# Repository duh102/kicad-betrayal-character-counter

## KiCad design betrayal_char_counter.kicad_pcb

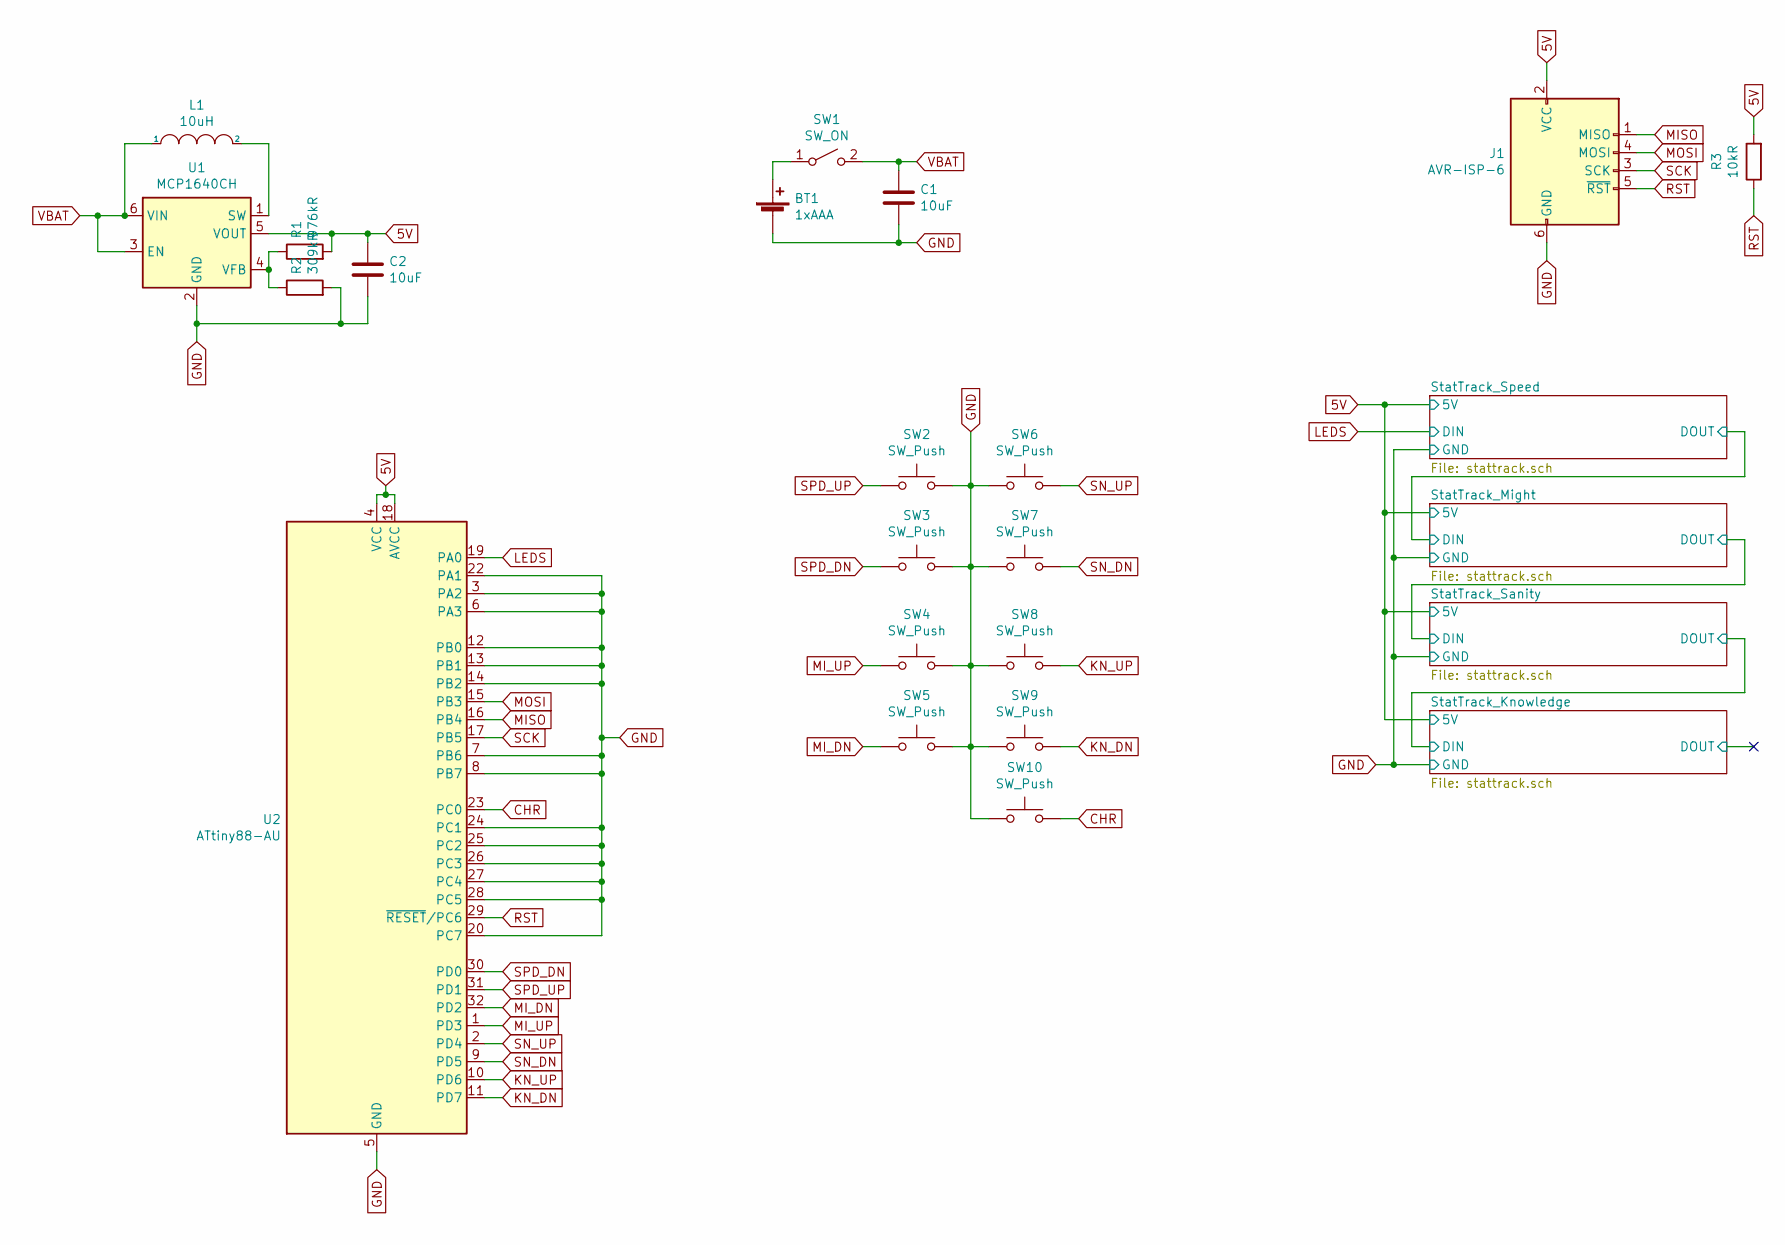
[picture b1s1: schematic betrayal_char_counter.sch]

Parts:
BT1: 1xAAA; BatteryHolder_Keystone_2466_1xAAA
C1, C2: 10uF; C_0805_2012Metric
J1: AVR-ISP-6; PinHeader_2x03_P2.54mm_Vertical_SMD
L1: 10uH; L_Taiyo-Yuden_NR-50xx
R1: 976kR; R_0805_2012Metric
R2: 309kR; R_0805_2012Metric
R3: 10kR; R_0805_2012Metric
SW1: SW_ON; SW_Slide_1P2T_CK_OS102011MS2Q
SW2, SW3, SW4, SW5, SW6, SW7, SW8, SW9, SW10: SW_Push; SW_SPST_SKQG_WithoutStem
U1: MCP1640CH; SOT-23-6
U2: ATtiny88-AU; TQFP-32_7x7mm_P0.8mm

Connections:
5V: C2.1, J1.2 (VCC), R1.2, R3.2, U1.5 (VOUT), U2.4 (VCC), U2.18 (AVCC); also elsewhere on the board
CHR: SW10.2, U2.23 (PC0)
GND: BT1.2 (-), C1.2, C2.2, J1.6 (GND), R2.2, SW2.2, SW3.2, SW4.2, SW5.2, SW6.1, SW7.1, SW8.1, SW9.1, SW10.1, U1.2 (GND), U2.3 (PA2), U2.5 (GND), U2.6 (PA3), U2.7 (PB6), U2.8 (PB7), U2.12 (PB0), U2.13 (PB1), U2.14 (PB2), U2.20 (PC7), U2.21 (GND), U2.22 (PA1), U2.24 (PC1), U2.25 (PC2), U2.26 (PC3), U2.27 (PC4), U2.28 (PC5); also elsewhere on the board
KN_DN: SW9.2, U2.11 (PD7)
KN_UP: SW8.2, U2.10 (PD6)
LEDS: U2.19 (PA0); also elsewhere on the board
MISO: J1.1 (MISO), U2.16 (PB4)
MI_DN: SW5.1, U2.32 (PD2)
MI_UP: SW4.1, U2.1 (PD3)
MOSI: J1.4 (MOSI), U2.15 (PB3)
unnamed: BT1.1 (+), SW1.1 (A)
unnamed: L1.2, U1.1 (SW)
unnamed: R1.1, R2.1, U1.4 (VFB)
RST: J1.5 (~RST), R3.1, U2.29 (~RESET~/PC6)
SCK: J1.3 (SCK), U2.17 (PB5)
SN_DN: SW7.2, U2.9 (PD5)
SN_UP: SW6.2, U2.2 (PD4)
SPD_DN: SW3.1, U2.30 (PD0)
SPD_UP: SW2.1, U2.31 (PD1)
VBAT: C1.1, L1.1, SW1.2 (B), U1.3 (EN), U1.6 (VIN)

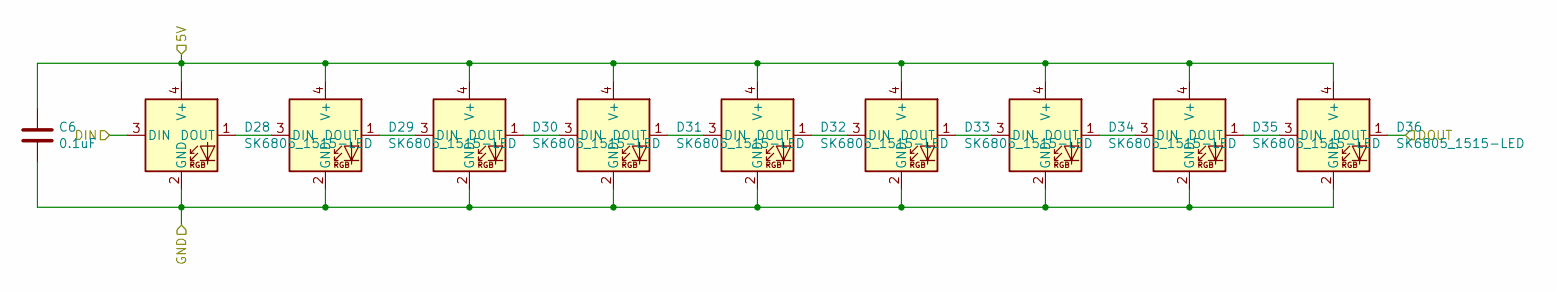
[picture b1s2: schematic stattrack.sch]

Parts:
C3: 0.1uF; C_0805_2012Metric
D1, D2, D3, D4, D5, D6, D7, D8, D9: SK6805_1515-LED; LED_SK6805_PLCC4_1.5x1.5mm_P0.65mm

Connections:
5V: C3.1, D1.4 (V+), D2.4 (V+), D3.4 (V+), D4.4 (V+), D5.4 (V+), D6.4 (V+), D7.4 (V+), D8.4 (V+), D9.4 (V+); also elsewhere on the board
/StatTrack_Might/DIN: D9.1 (DOUT); also elsewhere on the board
GND: C3.2, D1.2 (GND), D2.2 (GND), D3.2 (GND), D4.2 (GND), D5.2 (GND), D6.2 (GND), D7.2 (GND), D8.2 (GND), D9.2 (GND); also elsewhere on the board
LEDS: D1.3 (DIN); also elsewhere on the board
unnamed: D1.1 (DOUT), D2.3 (DIN)
unnamed: D2.1 (DOUT), D3.3 (DIN)
unnamed: D3.1 (DOUT), D4.3 (DIN)
unnamed: D4.1 (DOUT), D5.3 (DIN)
unnamed: D5.1 (DOUT), D6.3 (DIN)
unnamed: D6.1 (DOUT), D7.3 (DIN)
unnamed: D7.1 (DOUT), D8.3 (DIN)
unnamed: D8.1 (DOUT), D9.3 (DIN)

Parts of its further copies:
C4, C5, C6: 0.1uF; C_0805_2012Metric
D10, D11, D12, D13, D14, D15, D16, D17, D18, D19, D20, D21, D22, D23, D24, D25, D26, D27, D28, D29, D30, D31, D32, D33, D34, D35, D36: SK6805_1515-LED; LED_SK6805_PLCC4_1.5x1.5mm_P0.65mm

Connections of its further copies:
5V: C4.1, C5.1, C6.1, D10.4 (V+), D11.4 (V+), D12.4 (V+), D13.4 (V+), D14.4 (V+), D15.4 (V+), D16.4 (V+), D17.4 (V+), D18.4 (V+), D19.4 (V+), D20.4 (V+), D21.4 (V+), D22.4 (V+), D23.4 (V+), D24.4 (V+), D25.4 (V+), D26.4 (V+), D27.4 (V+), D28.4 (V+), D29.4 (V+), D30.4 (V+), D31.4 (V+), D32.4 (V+), D33.4 (V+), D34.4 (V+), D35.4 (V+), D36.4 (V+); also elsewhere on the board
/StatTrack_Knowledge/DIN: D27.1 (DOUT), D28.3 (DIN)
/StatTrack_Might/DIN: D10.3 (DIN); also elsewhere on the board
/StatTrack_Sanity/DIN: D18.1 (DOUT), D19.3 (DIN)
GND: C4.2, C5.2, C6.2, D10.2 (GND), D11.2 (GND), D12.2 (GND), D13.2 (GND), D14.2 (GND), D15.2 (GND), D16.2 (GND), D17.2 (GND), D18.2 (GND), D19.2 (GND), D20.2 (GND), D21.2 (GND), D22.2 (GND), D23.2 (GND), D24.2 (GND), D25.2 (GND), D26.2 (GND), D27.2 (GND), D28.2 (GND), D29.2 (GND), D30.2 (GND), D31.2 (GND), D32.2 (GND), D33.2 (GND), D34.2 (GND), D35.2 (GND), D36.2 (GND); also elsewhere on the board
unnamed: D10.1 (DOUT), D11.3 (DIN)
unnamed: D11.1 (DOUT), D12.3 (DIN)
unnamed: D12.1 (DOUT), D13.3 (DIN)
unnamed: D13.1 (DOUT), D14.3 (DIN)
unnamed: D14.1 (DOUT), D15.3 (DIN)
unnamed: D15.1 (DOUT), D16.3 (DIN)
unnamed: D16.1 (DOUT), D17.3 (DIN)
unnamed: D17.1 (DOUT), D18.3 (DIN)
unnamed: D19.1 (DOUT), D20.3 (DIN)
unnamed: D20.1 (DOUT), D21.3 (DIN)
unnamed: D21.1 (DOUT), D22.3 (DIN)
unnamed: D22.1 (DOUT), D23.3 (DIN)
unnamed: D23.1 (DOUT), D24.3 (DIN)
unnamed: D24.1 (DOUT), D25.3 (DIN)
unnamed: D25.1 (DOUT), D26.3 (DIN)
unnamed: D26.1 (DOUT), D27.3 (DIN)
unnamed: D28.1 (DOUT), D29.3 (DIN)
unnamed: D29.1 (DOUT), D30.3 (DIN)
unnamed: D30.1 (DOUT), D31.3 (DIN)
unnamed: D31.1 (DOUT), D32.3 (DIN)
unnamed: D32.1 (DOUT), D33.3 (DIN)
unnamed: D33.1 (DOUT), D34.3 (DIN)
unnamed: D34.1 (DOUT), D35.3 (DIN)
unnamed: D35.1 (DOUT), D36.3 (DIN)

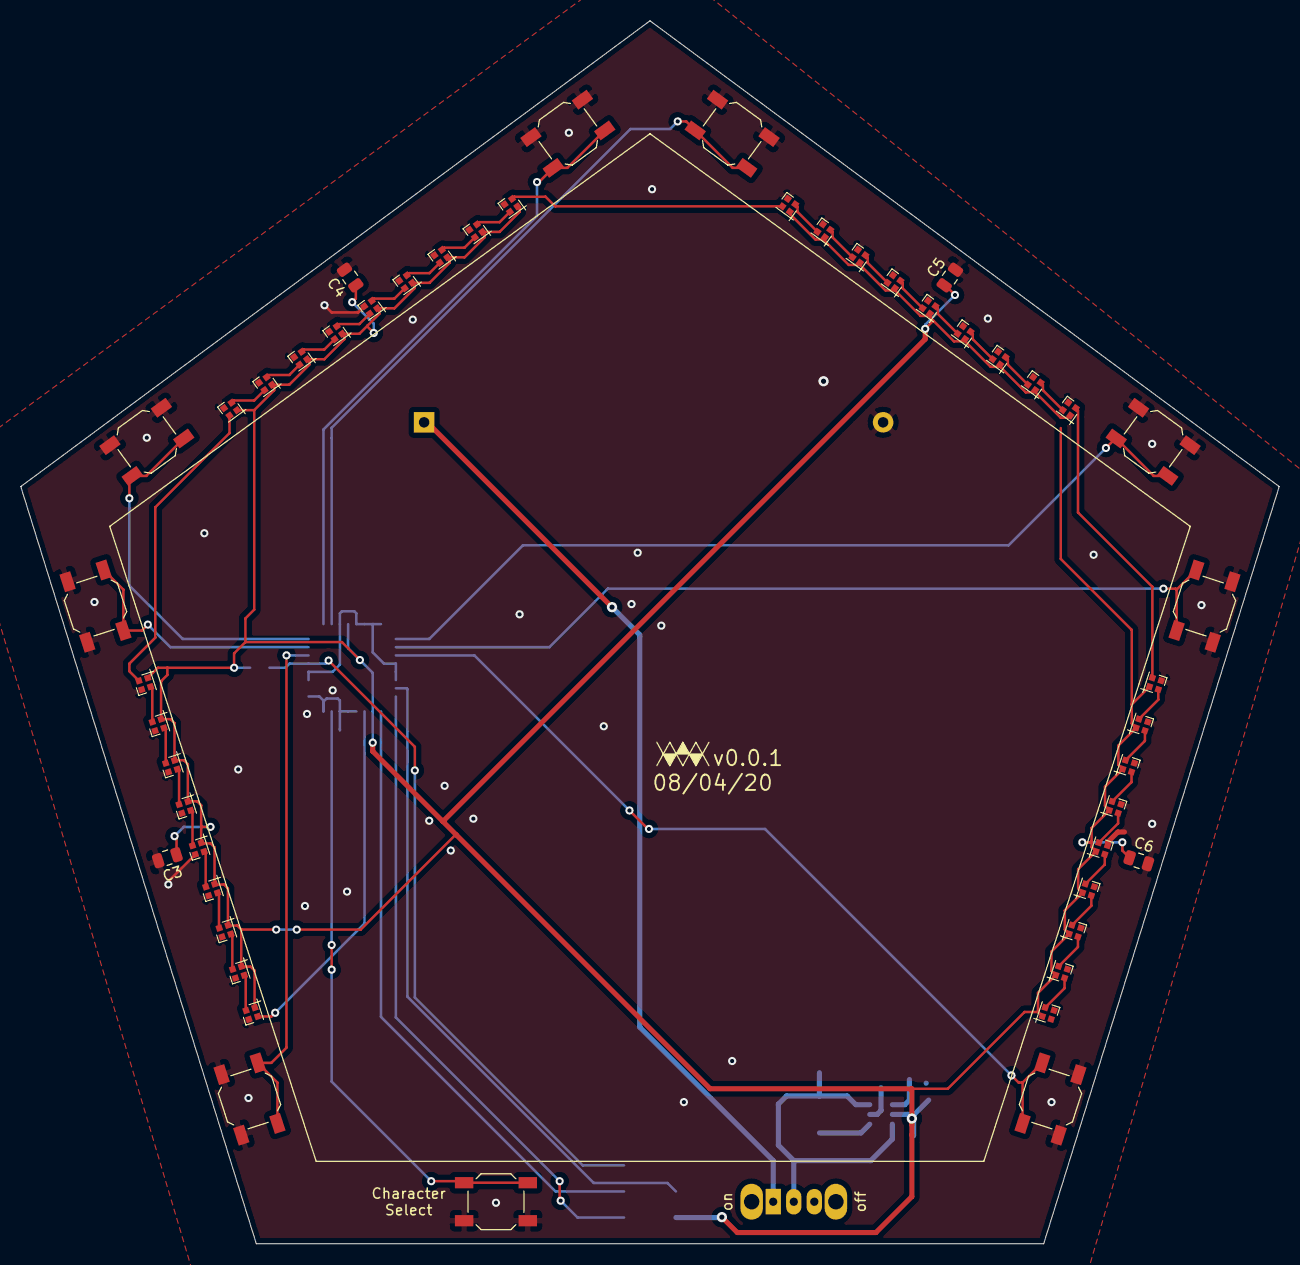
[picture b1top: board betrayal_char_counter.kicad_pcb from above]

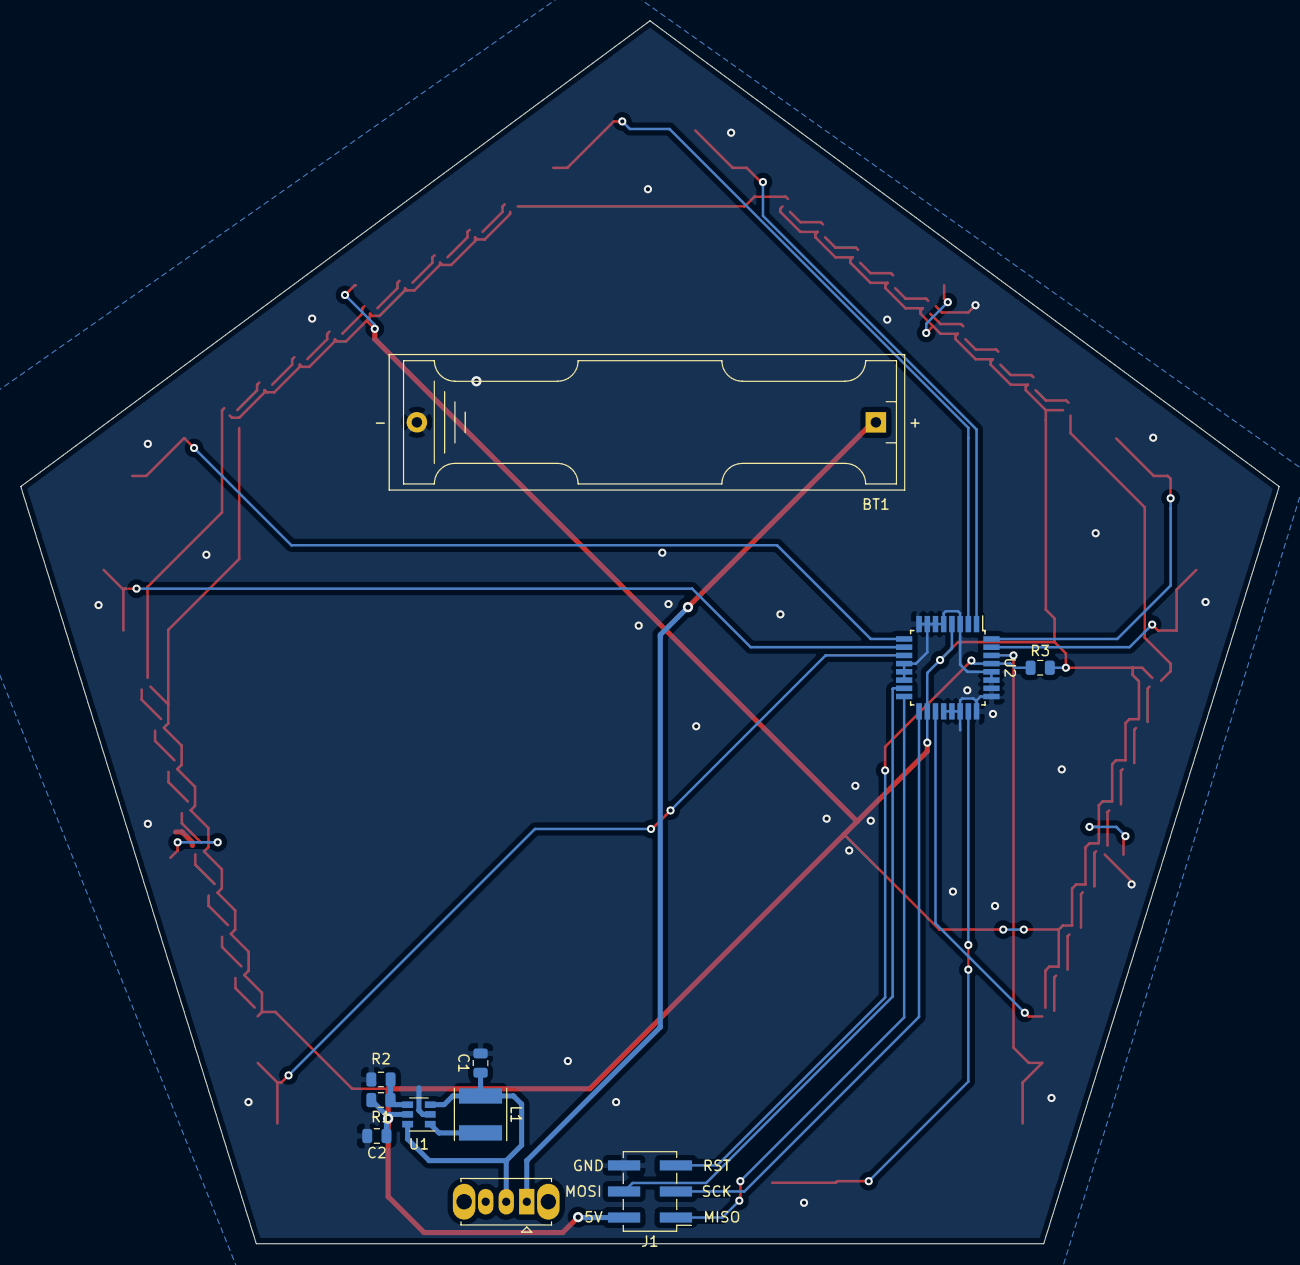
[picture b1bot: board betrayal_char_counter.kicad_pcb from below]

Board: 2 copper layers, 122.5 x 119.1 mm, 60 parts (11 on the bottom side), 55 nets.

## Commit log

2020-08-04 Add 1mm height
